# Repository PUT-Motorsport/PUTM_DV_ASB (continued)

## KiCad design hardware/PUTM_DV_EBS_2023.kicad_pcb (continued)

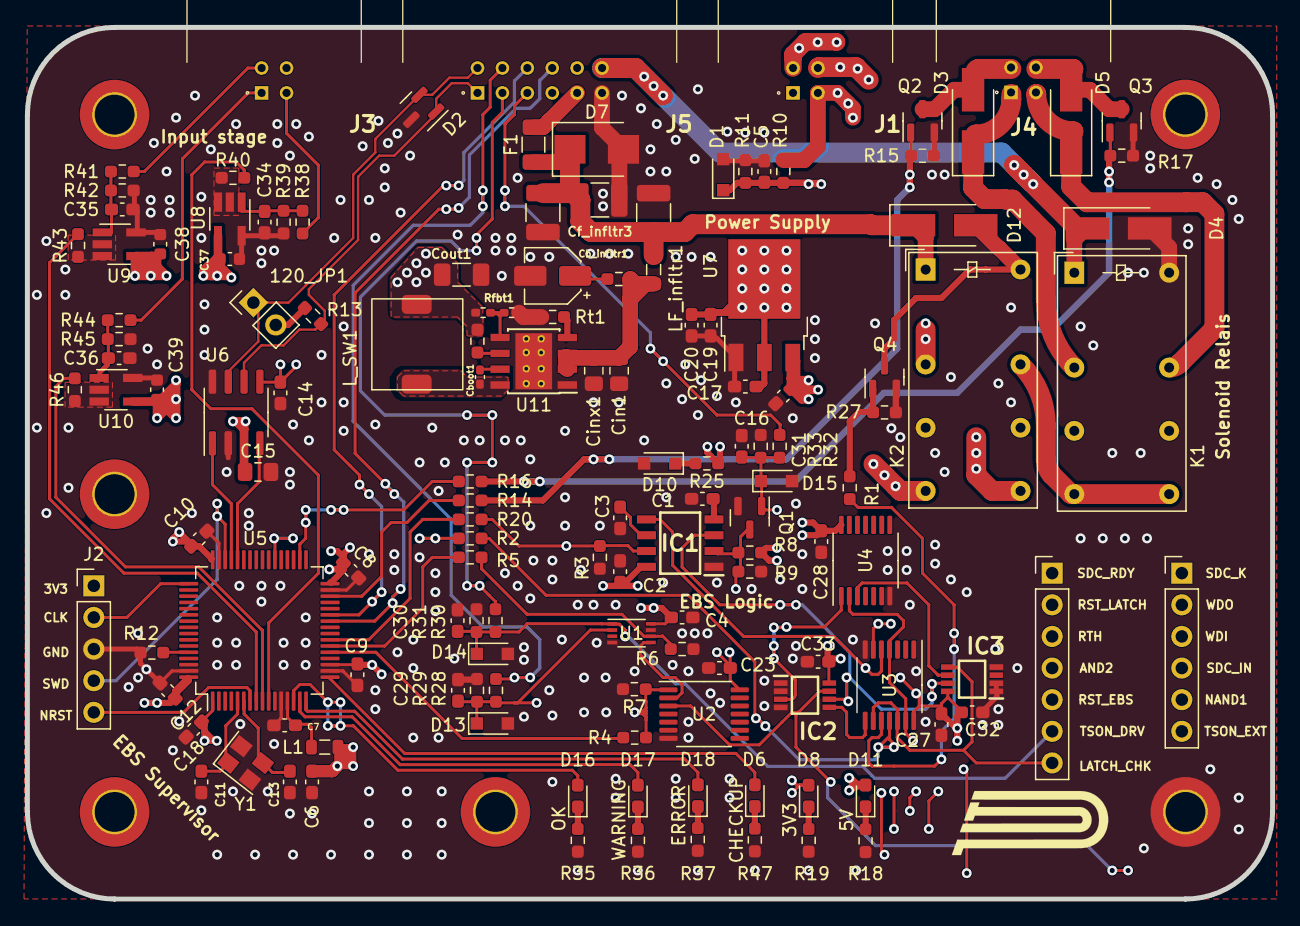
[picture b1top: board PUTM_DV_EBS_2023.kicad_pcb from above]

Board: 4 copper layers, 100.0 x 70.0 mm, 145 parts (0 on the bottom side), 92 nets.

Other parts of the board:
H1, H2, H3, H4, H5, H6: MountingHole_3.2mm_M3_DIN965_Pad_TopBottom
PUTM_LOGO: LOGO; PUTM_LOGO_15mm
TP1: PinHeader_1x07_P2.54mm_Vertical
TP2: PinHeader_1x06_P2.54mm_Vertical
U9, U10: TSX7191; SOT-23-5_HandSoldering

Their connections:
+5V: U9.4 (V+), U10.4 (V+); also elsewhere on the board
/EBS Logic/AS COMMANDS OK: TP2.5; also elsewhere on the board
/EBS Logic/AS_CLOSE_SDC: TP2.1; also elsewhere on the board
/EBS Logic/RESET BUTTON LATCH: TP1.2; also elsewhere on the board
/EBS Logic/SAFETY_IN: TP2.4; also elsewhere on the board
/EBS Logic/SAFETY_LATCH_CHK: TP1.7; also elsewhere on the board
/EBS Logic/SAFETY_RESET_BUT: TP1.5; also elsewhere on the board
/EBS Logic/SDC READY: TP1.1; also elsewhere on the board
/EBS Logic/TS_ON_COCKPIT: TP1.6; also elsewhere on the board
/EBS Logic/TS_ON_EXT: TP2.6; also elsewhere on the board
/EBS Logic/WATCHDOG: TP2.3; also elsewhere on the board
/EBS Logic/WD + SAFETY OK: TP1.4; also elsewhere on the board
GND: H5.1, U9.5 (V-), U10.5 (V-); also elsewhere on the board
unnamed 53: U9.1 (+); also elsewhere on the board
unnamed 54: U10.1 (+); also elsewhere on the board
unnamed 65: TP1.3; also elsewhere on the board
unnamed 66: TP2.2; also elsewhere on the board
unnamed 78: U9.2 (-), U9.3; also elsewhere on the board
unnamed 79: U10.2 (-), U10.3; also elsewhere on the board

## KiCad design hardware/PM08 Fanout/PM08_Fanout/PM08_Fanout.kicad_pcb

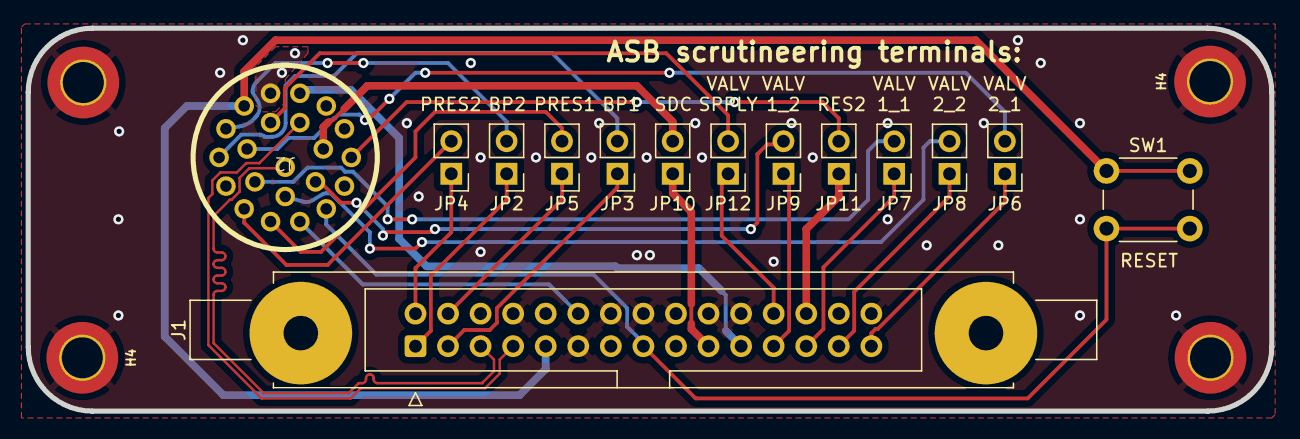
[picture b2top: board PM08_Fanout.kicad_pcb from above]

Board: 2 copper layers, 97.0 x 29.9 mm, 18 parts (0 on the bottom side), 28 nets.

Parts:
H3, H3#2, H4, H4#2: MountingHole_Pad; MountingHole_3.2mm_M3_DIN965_Pad_TopBottom
J1: IDC Connector; IDC-Header_2x15-1MP_P2.54mm_Latch6.5mm_Vertical
J2: 8STA 22pin; AS612-35PN
JP2, JP3, JP4, JP5, JP6, JP7, JP8, JP9, JP10, JP11, JP12: Jumper_2_Open; PinHeader_1x02_P2.54mm_Vertical
SW1: SW_SPST; SW_PUSH_6mm

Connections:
24v input: J1.9, J2.2, SW1.1 (A)
/ASMS: J2.11, JP11.2 (B)
/AirPressure1: J2.7, JP5.2 (B)
/AirPressure2: J2.6, JP4.2 (B)
/BrakePressure1: J2.4, JP3.2 (B)
/BrakePressure2: J2.3, JP2.2 (B)
/SDC_IN: J2.20, JP10.2 (B)
/solenoid1_I: J2.17, JP7.2 (B)
/solenoid1_II: J2.19, JP9.2 (B)
/solenoid2_I: J2.16, JP6.2 (B)
/solenoid2_II: J2.18, JP8.2 (B)
AUX1: J1.12, J2.8
CAN+: J1.5, J2.22
CAN-: J1.7, J2.21
EBS_RESET _BUTTON: J1.15, J2.9, SW1.2 (B)
GND: H3.1, H3#2.1, H4.1, H4#2.1, J1.6, J1.8, J1.11, J1.14, J1.16, J1.18, J1.20, J1.22, J1.28, J1.30, J2.1
LINE: J1.26, JP11.1 (A)
SAFETY_IN: J1.19, JP10.1 (A)
SAFETY_OUT: J1.21, J2.14
SENSORIN_EBS: J1.2, JP4.1 (A)
SENSORIN_MAIN: J1.4, JP5.1 (A)
SENSORIN_REDUNDANT: J1.3, JP3.1 (A)
SENSORIN_SPARE: J1.1, JP2.1 (A)
TSMS: J1.24, J2.15, JP12.1 (A), JP12.2 (B)
VALVE_1_COIL_I: J1.25, JP7.1 (A)
VALVE_1_COIL_II: J1.23, JP9.1 (A)
VALVE_2_COIL_I: J1.29, JP6.1 (A)
VALVE_2_COIL_II: J1.27, JP8.1 (A)

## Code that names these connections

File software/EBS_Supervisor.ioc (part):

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Mcu.Name=STM32F103R(8-B)Tx
Mcu.Package=LQFP64
Mcu.UserName=STM32F103R8Tx
PA0-WKUP.GPIOParameters=GPIO_Label
PA0-WKUP.GPIO_Label=LD_OK
PA0-WKUP.Signal=GPIO_Output
PA1.GPIOParameters=GPIO_Label
PA1.GPIO_Label=LD_WARN
PA1.Signal=GPIO_Output
PA11.Mode=CAN_Activate
PA11.Signal=CAN_RX
PA12.Mode=CAN_Activate
PA12.Signal=CAN_TX
PA13.Mode=Serial_Wire
PA13.Signal=SYS_JTMS-SWDIO
PA14.Mode=Serial_Wire
PA14.Signal=SYS_JTCK-SWCLK
PA2.GPIOParameters=GPIO_Label
PA2.GPIO_Label=LD_ERROR
PA2.Signal=GPIO_Input
PA3.GPIOParameters=GPIO_Label
PA3.GPIO_Label=LD_CHK
PA3.Signal=GPIO_Output
PA5.GPIOParameters=GPIO_Label
PA5.GPIO_Label=AS_CLOSE_SDC
PA5.Signal=GPIO_Output
PA6.GPIOParameters=GPIO_Label
PA6.GPIO_Label=AS_MODE
PA6.Signal=GPIO_Output
PA7.Signal=S_TIM3_CH2
PB0.GPIOParameters=GPIO_Label
PB0.GPIO_Label=spare1
PB0.Signal=GPIO_Output
PB1.GPIOParameters=GPIO_Label
PB1.GPIO_Label=spare2
PB1.Signal=GPIO_Output
PB11.GPIOParameters=GPIO_Label
PB11.GPIO_Label=VALVE1
PB11.Signal=GPIO_Output
PB13.GPIOParameters=GPIO_Label
PB13.GPIO_Label=VALVE2
PB13.Signal=GPIO_Output
PC0.GPIOParameters=GPIO_Label
PC0.GPIO_Label=AIR_EBS
PC0.Signal=ADCx_IN10
PC1.GPIOParameters=GPIO_Label
PC1.GPIO_Label=AIR_RDNT
PC1.Signal=ADCx_IN11
PC2.GPIOParameters=GPIO_Label
PC2.GPIO_Label=AIR_MAIN
PC2.Signal=ADCx_IN12
PC7.GPIOParameters=GPIO_Label
PC7.GPIO_Label=SDC_RDY
PC7.Signal=GPIO_Input
PD0-OSC_IN.Mode=HSE-External-Oscillator
PD0-OSC_IN.Signal=RCC_OSC_IN
PD1-OSC_OUT.Mode=HSE-External-Oscillator
PD1-OSC_OUT.Signal=RCC_OSC_OUT
RCC.SYSCLKFreq_VALUE=72000000
RCC.SYSCLKSource=RCC_SYSCLKSOURCE_PLLCLK
board=custom

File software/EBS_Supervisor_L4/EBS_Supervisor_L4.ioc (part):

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Mcu.Name=STM32L4P5R(G-E)Tx
Mcu.Package=LQFP64
Mcu.UserName=STM32L4P5RETx
PA0.GPIOParameters=GPIO_Label
PA0.GPIO_Label=LD_OK
PA0.Signal=GPIO_Output
PA1.GPIOParameters=GPIO_Label
PA1.GPIO_Label=LD_WARN
PA1.Signal=GPIO_Output
PA11.Mode=CAN_Activate
PA11.Signal=CAN1_RX
PA12.Mode=CAN_Activate
PA12.Signal=CAN1_TX
PA13\ (JTMS/SWDIO).Mode=Serial_Wire
PA13\ (JTMS/SWDIO).Signal=SYS_JTMS-SWDIO
PA14\ (JTCK/SWCLK).Mode=Serial_Wire
PA14\ (JTCK/SWCLK).Signal=SYS_JTCK-SWCLK
PA2.GPIOParameters=GPIO_Label
PA2.GPIO_Label=LD_ERR
PA2.Signal=GPIO_Output
PA3.GPIOParameters=GPIO_Label
PA3.GPIO_Label=LD_CHK
PA3.Signal=GPIO_Output
PA5.GPIOParameters=GPIO_Label
PA5.GPIO_Label=AS_CLOSE_SDC
PA5.Signal=GPIO_Output
PA6.GPIOParameters=GPIO_Label
PA6.GPIO_Label=AS_MODE
PA6.Signal=GPIO_Output
PA7.Signal=S_TIM3_CH2
PB11.GPIOParameters=GPIO_Label
PB11.GPIO_Label=VALVE1
PB11.Signal=GPIO_Output
PB13.GPIOParameters=GPIO_Label
PB13.GPIO_Label=VALVE2
PB13.Signal=GPIO_Output
PC0.GPIOParameters=GPIO_Label
PC0.GPIO_Label=AIR_EBS
PC0.Signal=ADCx_IN1
PC1.GPIOParameters=GPIO_Label
PC1.GPIO_Label=AIR_RDNT
PC1.Signal=ADCx_IN2
PC2.GPIOParameters=GPIO_Label
PC2.GPIO_Label=AIR_MAIN
PC2.Signal=ADCx_IN3
PC7.GPIOParameters=GPIO_Label
PC7.GPIO_Label=SDC_RDY
PC7.Signal=GPIO_Input
PH0-OSC_IN\ (PH0).Mode=HSE-External-Oscillator
PH0-OSC_IN\ (PH0).Signal=RCC_OSC_IN
PH1-OSC_OUT\ (PH1).Mode=HSE-External-Oscillator
PH1-OSC_OUT\ (PH1).Signal=RCC_OSC_OUT
RCC.HSE_VALUE=16000000
RCC.SYSCLKFreq_VALUE=64000000
RCC.SYSCLKSource=RCC_SYSCLKSOURCE_PLLCLK
board=custom

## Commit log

2022-10-15 Initial commit, schematic v1
    Just making a little cleanup on GitHub
2022-10-15 added image to readme
2022-10-18 Fixed Logic
2022-10-18 Alpha 1.0.0 Schematic
    First Schematic Version for initial checkup
2022-10-20 Minor changes on v1 schematic
2022-11-05 minor schematic cleanup
    Fixes before second review
2022-11-05 Schematic ready for second review
    Cleaned up, numerated, added footprints, JW notes considered
2022-11-15 0xERC State
    Schematic needs only simulation and veryfying component choice for now
2022-11-19 Last schematic todo changes, mother slander on PCB
2022-12-05 working simulations, assigned footprints
    "nightly" relase
2022-12-06 minor changes
    pre spotkanie comiit ;DD
2022-12-06 kończymy balet na dziś
2022-12-08 begin of placement process, supply section done
    będą obłe ścieżki i chuj
2022-12-08 JLC fabrication adjustments, assigned nets
    sluchajcie historii typ jakis z ryjem do mnie na swiatlach AWF bo pozno ruszylem pozniej sie ustawilismy kolo siebie i go zjadlem na acceleration new beetlem bo ma 110 koni jebaniec pozdrawiam frajer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
2022-12-09 dobra ide spać
2022-12-10 full 3d models, pre-routing, corrections
    kurwa bezpiecznik od wczoraj a fura dalej nie jeździ siedze u rakietowcow bo cieplo chlopaki co z wami
2022-12-11 still working
2022-12-12 kurde no jeszcze nie skonczylem ale sune dalej
2022-12-14 fixed references addet tp;s mam pojutrze przejebany egzamin nara
2022-12-20 supply section redesign due to IC shortage
2022-12-20 routing update, new supply section routed
2022-12-21 PCB in review and DRC error delete state, please check it
2022-12-22 DRC fixes part 1
2022-12-23 Alpha 1.0 Hardware relase. 0xDRC state, improved aesthetics and signal integrity
2022-12-28 Last touches,PCB ready to order
2022-12-29 minor aestethics improvement
2023-01-04 GND improvement after Review (taka masa ze sie wengoz zesra)
2023-02-20 uga baga commmit hardware
2023-02-20 sofware
2023-02-21 Masz Piotruś
2023-03-04 added tests
2023-03-04 slight remake
2023-03-09 written most of the logic
2023-03-14 komit
2023-04-15 Removed unnecessary directories
2023-05-11 WoW took me like 5min
2023-05-26 Initial commit BP_readings
2023-05-26 clock issues
2023-07-07 L4 port
2023-07-13 first working state, valves forced activation
2023-09-18 Schematic redesign for 23 rules, new pressure buffer, protection fix
2023-09-20 WIP revision 2 layout refinement
2023-09-29 2.0 layot wip, each sections placed
2023-10-02 WIP 1.1 routing
2023-10-02 2.0 layot wip , routing 2
2023-10-03 2.0 layot wip , routing 3
2023-10-12 Dimensions compress, routing
2023-10-17 replace RES2 input to actuator relai
2023-10-23 Adjust mounting holes to FBOX and BSPD
2023-10-30 0xDRC state 1.1 ready for review
2023-11-17 Main board 1.1 production files
2023-11-18 Added PM08 connector board
2023-12-10 ADD ASB CAN header, working data send
2023-12-10 Succesful pressure value send over CAN, DMA fix
2026-03-14 Ported to cmake
2026-03-15 deleted old can
2026-03-15 added can library as git submodule
2026-03-16 can init
2026-03-17 Fixed cmake target_-lik_libraries problem
2026-03-17 can init and brake pressure receive callback
2026-03-17 fixed can callback
2026-03-17 added can filter
2026-03-17 changed main loop
2026-03-17 changed project layout
2026-03-17 renamed firmware
2026-03-19 added methods for checking pressure
2026-03-19 changed error handling
2026-03-19 fixed loop
2026-03-19 deleted unused functions
2026-03-22 fixed brake variable name
2026-03-22 Added error handling
2026-03-24 Changed gitignore
2026-03-24 Changed checkup
2026-03-26 changed pcb version
2026-03-31 uploaded older pcb version
2026-03-31 uncommented
2026-03-31 kicad 10 port
2026-04-06 fixed adc callback
2026-04-07 simplified error handling
2026-04-09 fixed adc reading
